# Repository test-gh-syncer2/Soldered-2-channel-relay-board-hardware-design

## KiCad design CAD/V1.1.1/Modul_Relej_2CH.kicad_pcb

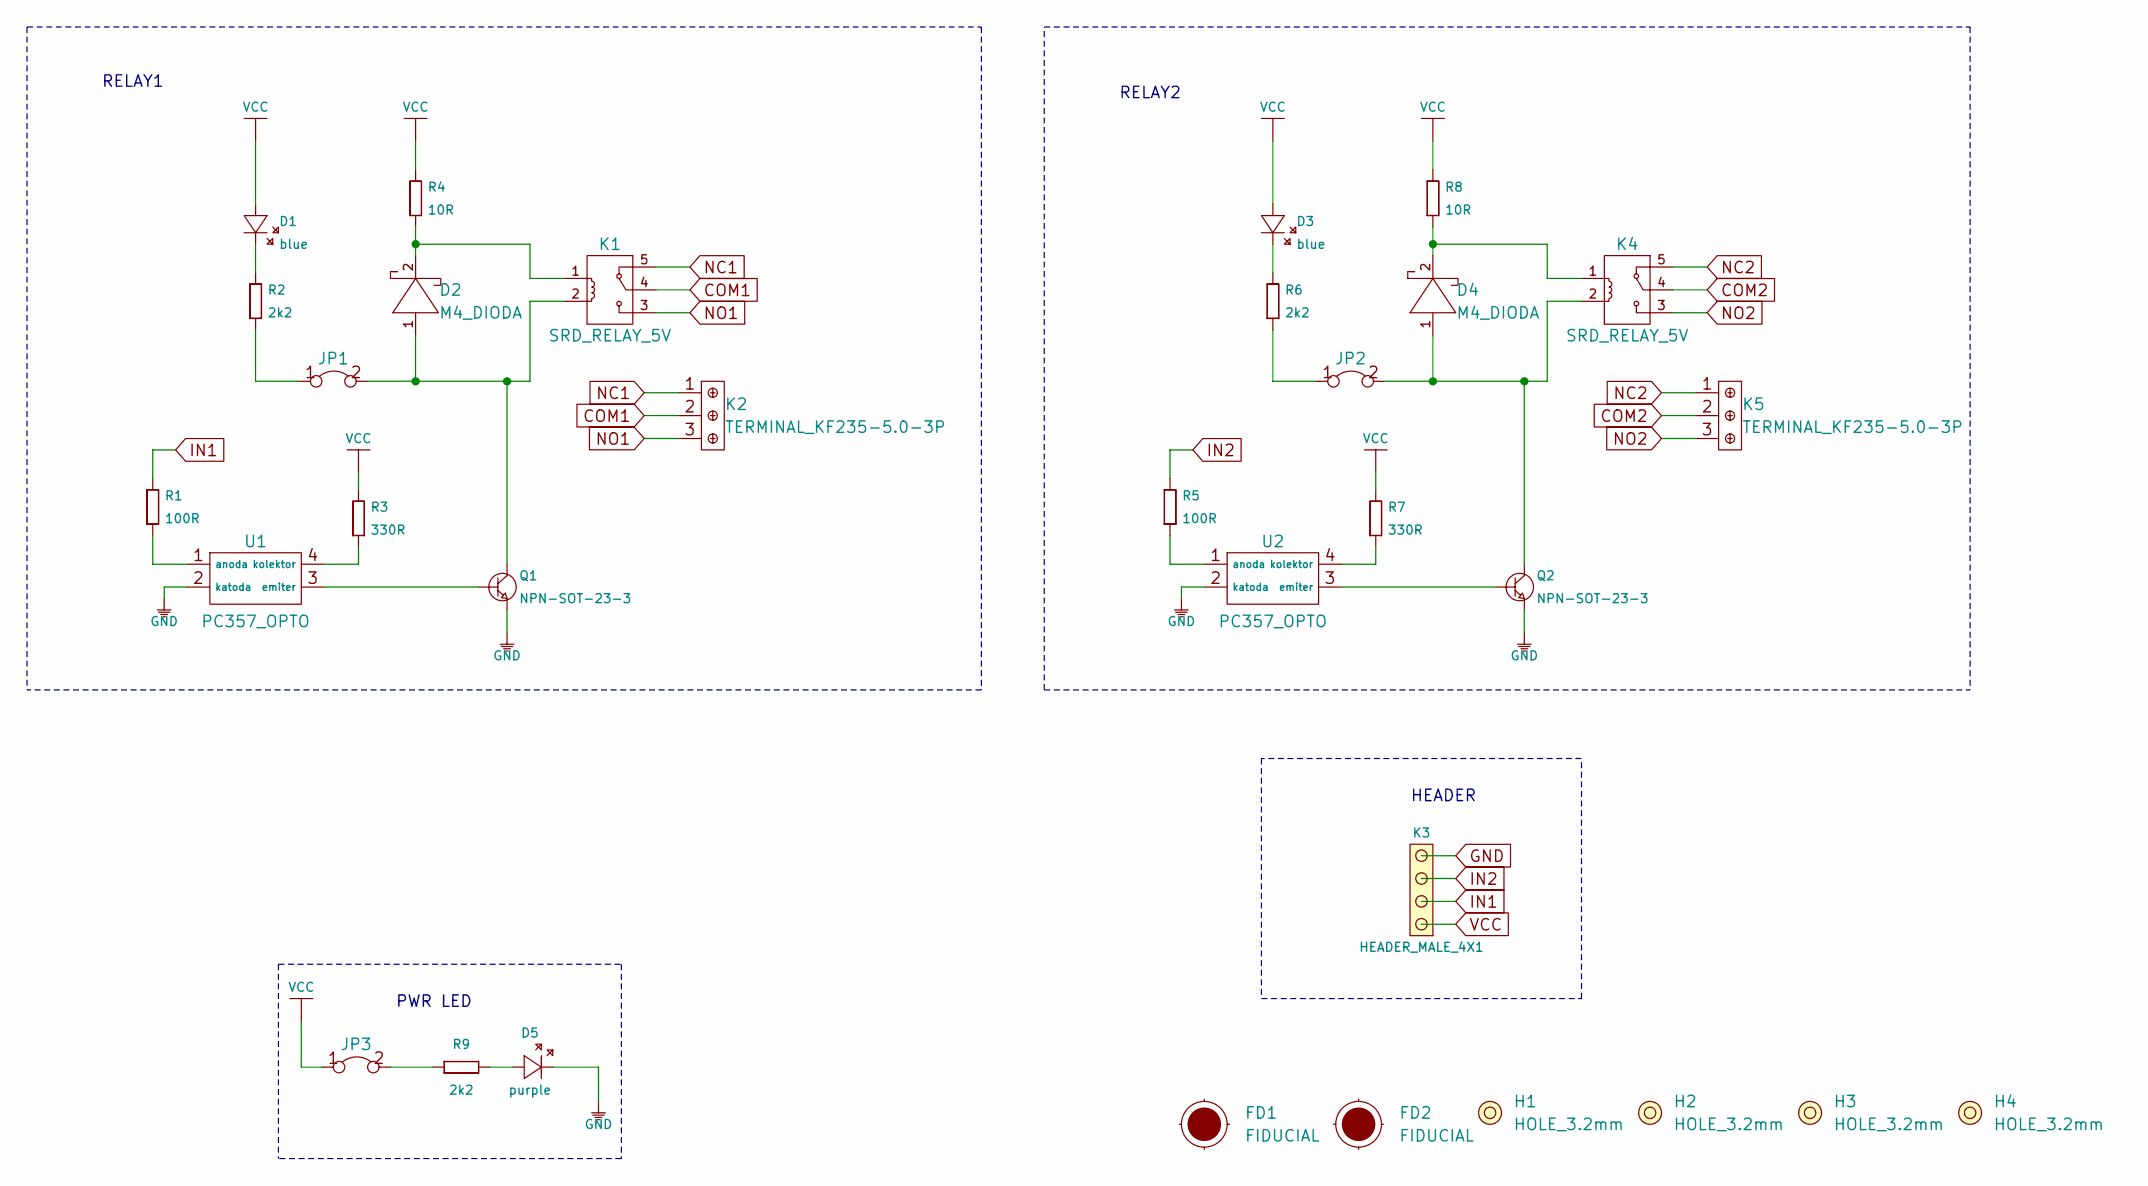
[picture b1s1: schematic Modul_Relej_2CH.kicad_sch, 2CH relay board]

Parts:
D1, D3: blue; 0402LED
D2, D4: M4_DIODA
D5: purple; 0402LED
FD1, FD2: FIDUCIAL; FIDUCIAL_23
H1, H2, H3, H4: HOLE_3.2mm
JP1, JP2, JP3: SMD-JUMPER-CONNECTED_TRACE_SLODERMASK
K1, K4: SRD_RELAY_5V
K2, K5: TERMINAL_KF235-5.0-3P
K3: HEADER_MALE_4X1
Q1, Q2: NPN-SOT-23-3; SOT-23-3
R1, R5: 100R; 0603R
R2, R6, R9: 2k2; 0402R
R3, R7: 330R; 0603R
R4, R8: 10R; 0603R
U1, U2: PC357_OPTO

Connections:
COM1: K1.4, K2.2
COM2: K4.4, K5.2
GND: D5.2 (K), K3.4, Q1.2 (E), Q2.2 (E), U1.2 (katoda), U2.2 (katoda)
IN1: K3.2, R1.2
IN2: K3.3, R5.2
NC1: K1.5, K2.1
NC2: K4.5, K5.1
NO1: K1.3, K2.3
NO2: K4.3, K5.3
unnamed: D1.2 (K), R2.2
unnamed: D2.1 (A), JP1.2, K1.2, Q1.3 (C)
unnamed: D2.2 (K), K1.1, R4.1
unnamed: D3.2 (K), R6.2
unnamed: D4.1 (A), JP2.2, K4.2, Q2.3 (C)
unnamed: D4.2 (K), K4.1, R8.1
unnamed: D5.1 (A), R9.2
unnamed: JP1.1, R2.1
unnamed: JP2.1, R6.1
unnamed: JP3.2, R9.1
unnamed: Q1.1 (B), U1.3 (emiter)
unnamed: Q2.1 (B), U2.3 (emiter)
unnamed: R1.1, U1.1 (anoda)
unnamed: R3.1, U1.4 (kolektor)
unnamed: R5.1, U2.1 (anoda)
unnamed: R7.1, U2.4 (kolektor)
VCC: D1.1 (A), D3.1 (A), JP3.1, K3.1, R3.2, R4.2, R7.2, R8.2

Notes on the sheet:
RELAY1
PWR LED
RELAY2
HEADER

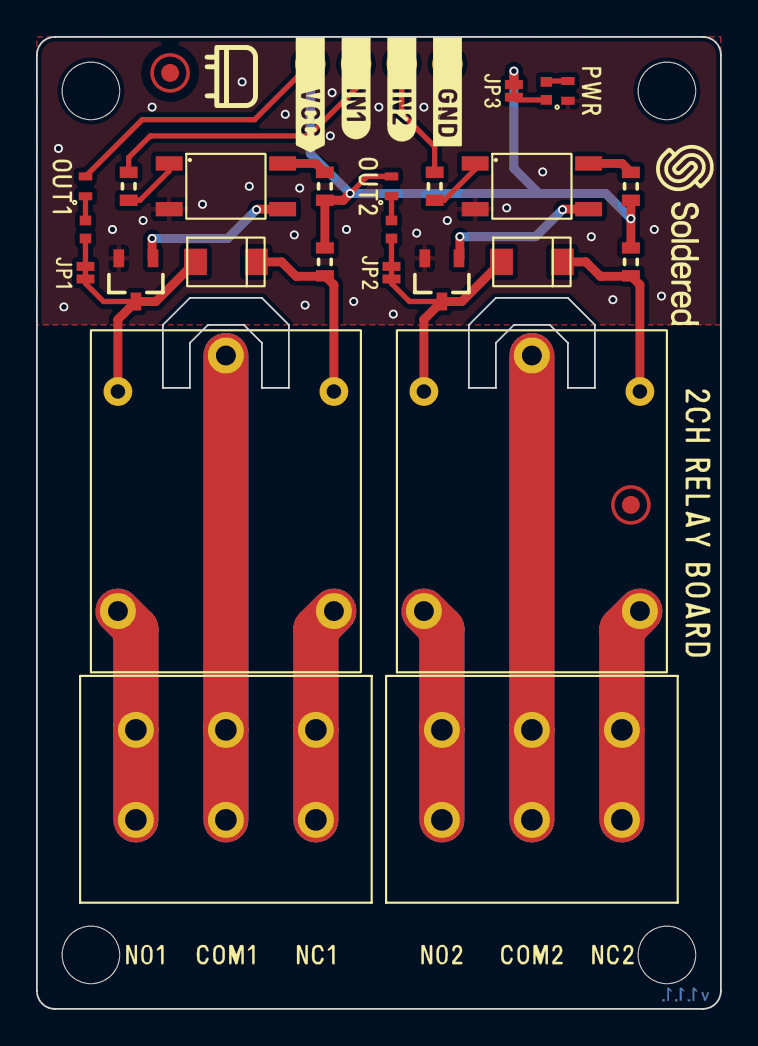
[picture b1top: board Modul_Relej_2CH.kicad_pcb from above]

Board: 2 copper layers, 38.0 x 54.0 mm, 32 parts (1 on the bottom side), 26 nets.

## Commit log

2021-09-23 Syncing to git
2021-09-23 Updating open source files.
